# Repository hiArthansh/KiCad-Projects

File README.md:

# KiCad-Projects
From schematic to PCB projects. 
Designing mini circuits from schematic to entire PCB layout fro learning and hands-on experience with the software.

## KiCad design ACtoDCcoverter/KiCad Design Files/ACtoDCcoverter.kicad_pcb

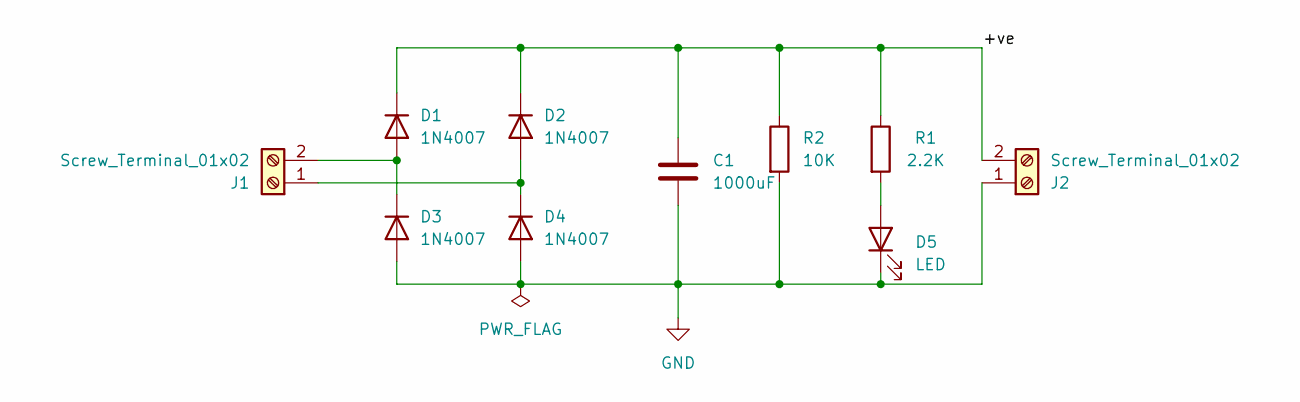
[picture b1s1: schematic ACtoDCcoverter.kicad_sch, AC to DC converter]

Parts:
C1: 1000uF; CP_Radial_D13.0mm_P5.00mm
D1, D2, D3, D4: 1N4007; D_DO-41_SOD81_P10.16mm_Horizontal
D5: LED; LED_D5.0mm
J1, J2: Screw_Terminal_01x02; Altech_AK100_1x02_P5.00mm
R1: 2.2K; R_Axial_DIN0204_L3.6mm_D1.6mm_P7.62mm_Horizontal
R2: 10K; R_Axial_DIN0204_L3.6mm_D1.6mm_P7.62mm_Horizontal

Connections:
/+ve: C1.1, D1.1 (K), D2.1 (K), J2.2, R1.1, R2.1
GND: C1.2, D3.2 (A), D4.2 (A), D5.1 (K), J2.1, R2.2
unnamed: D1.2 (A), D3.1 (K), J1.2
unnamed: D2.2 (A), D4.1 (K), J1.1
unnamed: D5.2 (A), R1.2

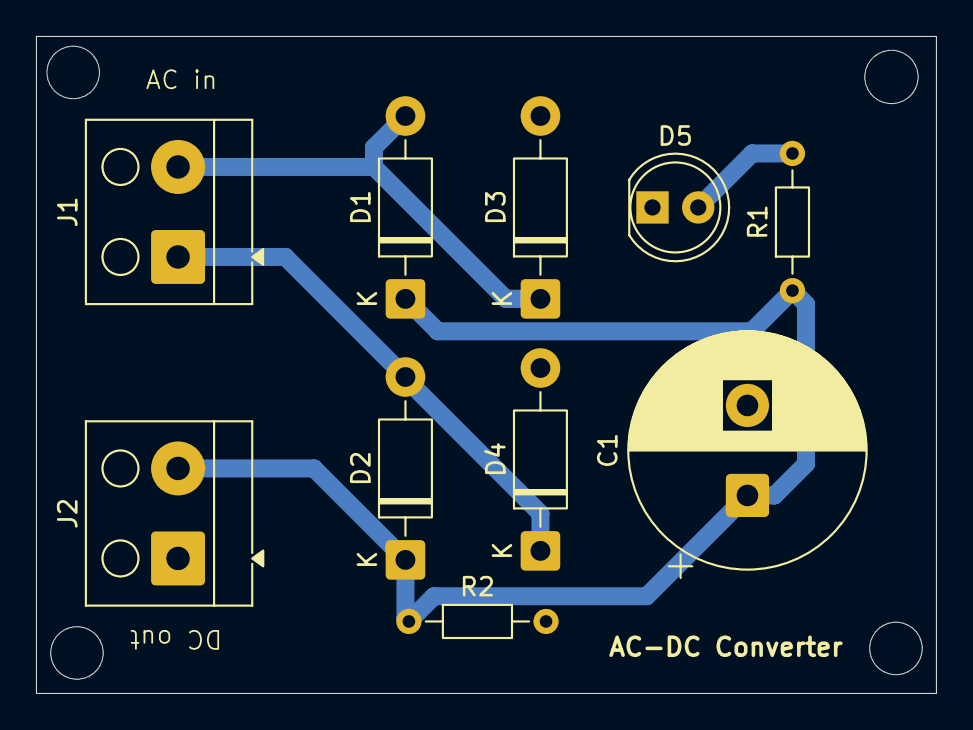
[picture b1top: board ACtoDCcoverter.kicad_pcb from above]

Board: 2 copper layers, 50.0 x 36.5 mm, 10 parts (0 on the bottom side), 5 nets.

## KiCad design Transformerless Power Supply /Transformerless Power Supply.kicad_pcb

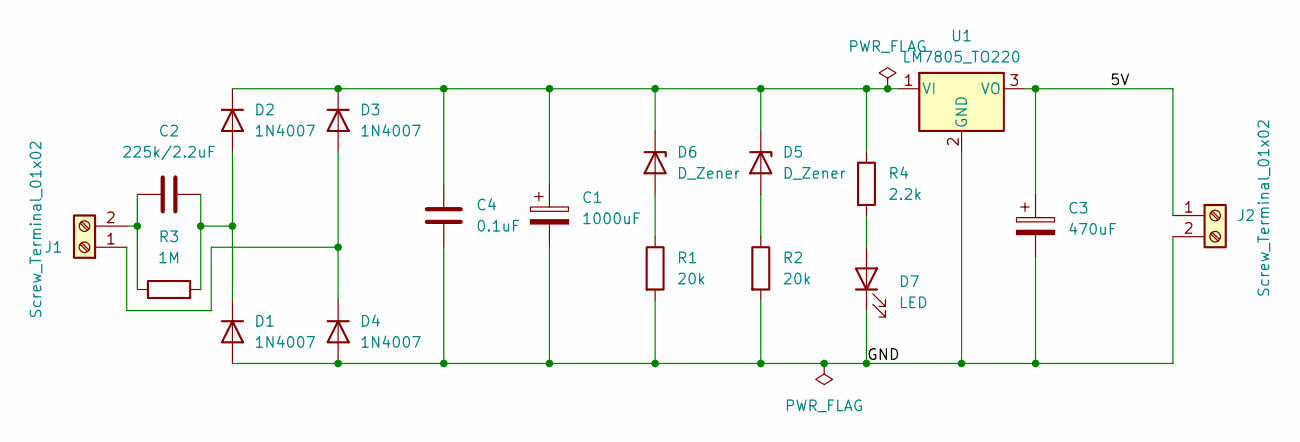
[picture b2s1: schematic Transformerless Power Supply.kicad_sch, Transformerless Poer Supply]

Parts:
C1: 1000uF; CP_Radial_D10.0mm_P5.00mm
C2: 225k/2.2uF; C_Rect_L19.0mm_W6.0mm_P15.00mm_MKS4
C3: 470uF; CP_Radial_D10.0mm_P3.80mm
C4: 0.1uF; C_Disc_D4.7mm_W2.5mm_P5.00mm
D1, D2, D3, D4: 1N4007; D_DO-41_SOD81_P10.16mm_Horizontal
D5, D6: D_Zener; D_A-405_P7.62mm_Horizontal
D7: LED; LED_D5.0mm
J1, J2: Screw_Terminal_01x02; Altech_AK100_1x02_P5.00mm
R1, R2: 20k; R_Axial_DIN0207_L6.3mm_D2.5mm_P7.62mm_Horizontal
R3: 1M; R_Axial_DIN0207_L6.3mm_D2.5mm_P7.62mm_Horizontal
R4: 2.2k; R_Axial_DIN0207_L6.3mm_D2.5mm_P7.62mm_Horizontal
U1: LM7805_TO220; TO-220-3_Vertical

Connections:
/5V: C3.1, J2.1, U1.3 (VO)
/GND: C1.2, C3.2, C4.1, D1.2 (A), D4.2 (A), D7.1 (K), J2.2, R1.2, R2.2, U1.2 (GND)
unnamed: C2.2, D1.1 (K), D2.2 (A), R3.2
unnamed: C1.1, C4.2, D2.1 (K), D3.1 (K), D5.1 (K), D6.1 (K), R4.1, U1.1 (VI)
unnamed: D3.2 (A), D4.1 (K), J1.1
unnamed: D5.2 (A), R2.1
unnamed: D6.2 (A), R1.1
unnamed: D7.2 (A), R4.2
unnamed: C2.1, J1.2, R3.1

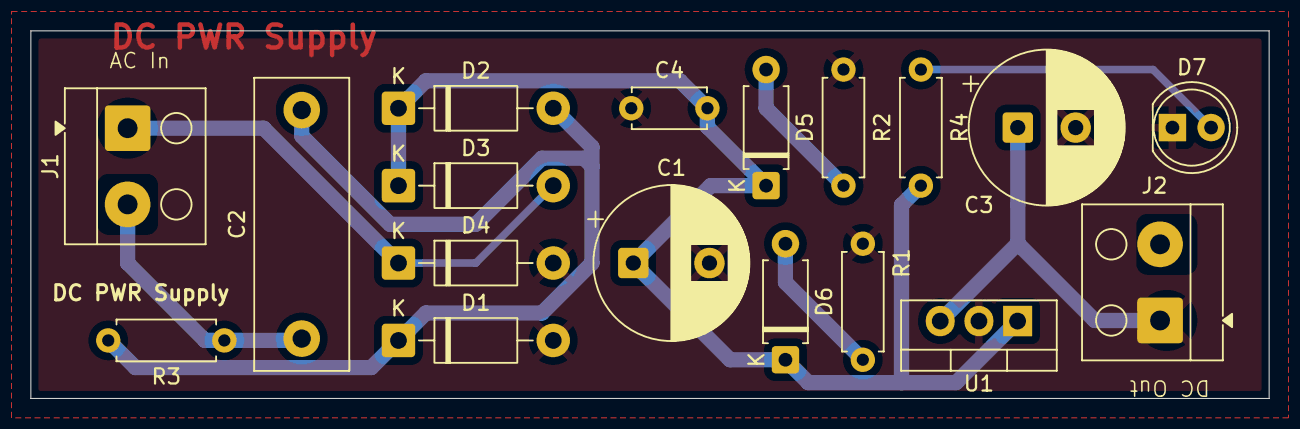
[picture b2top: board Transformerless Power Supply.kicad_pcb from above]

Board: 2 copper layers, 81.3 x 24.1 mm, 18 parts (0 on the bottom side), 9 nets.

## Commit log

2025-12-15 AC to DC Converter
    From Schematic to PCB layout AC to DC converter
2025-12-15 Problem faced witht heir solutions
2025-12-15 Rename exam_answers.pdf to Documentation.pdf
2025-12-15 Rename WhatsApp Video 2025-12-16 at 01.29.22.mp4 to PCB Video
2025-12-15 Rename image.png to PCB-back.png
2025-12-15 Rename ACtoDCcoverter/image.png to PCB-front.png
2025-12-15 Rename image.png to PCB-front.png
2025-12-15 Rename image.png to PCB-Editor.png
2025-12-15 Rename PCB-front.png to Schematic.png
2025-12-15 Create KiCad Project Files
2025-12-15 Create KiCad Design Files
2025-12-15 Rename PCB-front.png to ACtoDCcoverter/PCB-front.png
2025-12-16 Create DC PWR Supply
2025-12-16 Rename Schematic.png to Transformerless Power Supply/ Schematic.png
2025-12-16 Rename Transformerless Power Supply.kicad_prl to Transformerless Power Supply/Transformerless Power Supply.kicad_prl
2025-12-16 Rename Transformerless Power Supply.kicad_pro to Transformerless Power Supply/Transformerless Power Supply.kicad_pro
2025-12-16 Rename Transformerless Power Supply/Transformerless Power Supply.kicad_prl to Transformerless Power Supply/KiCad Design Files/Transformerless Power Supply.kicad_prl
2025-12-16 Rename Transformerless Power Supply/Transformerless Power Supply.kicad_pro to Transformerless Power Supply/KiCad Design Files/Transformerless Power Supply.kicad_pro
2025-12-16 Rename Transformerless Power Supply/fp-info-cache to Transformerless Power Supply/KiCad Design Files/fp-info-cache
